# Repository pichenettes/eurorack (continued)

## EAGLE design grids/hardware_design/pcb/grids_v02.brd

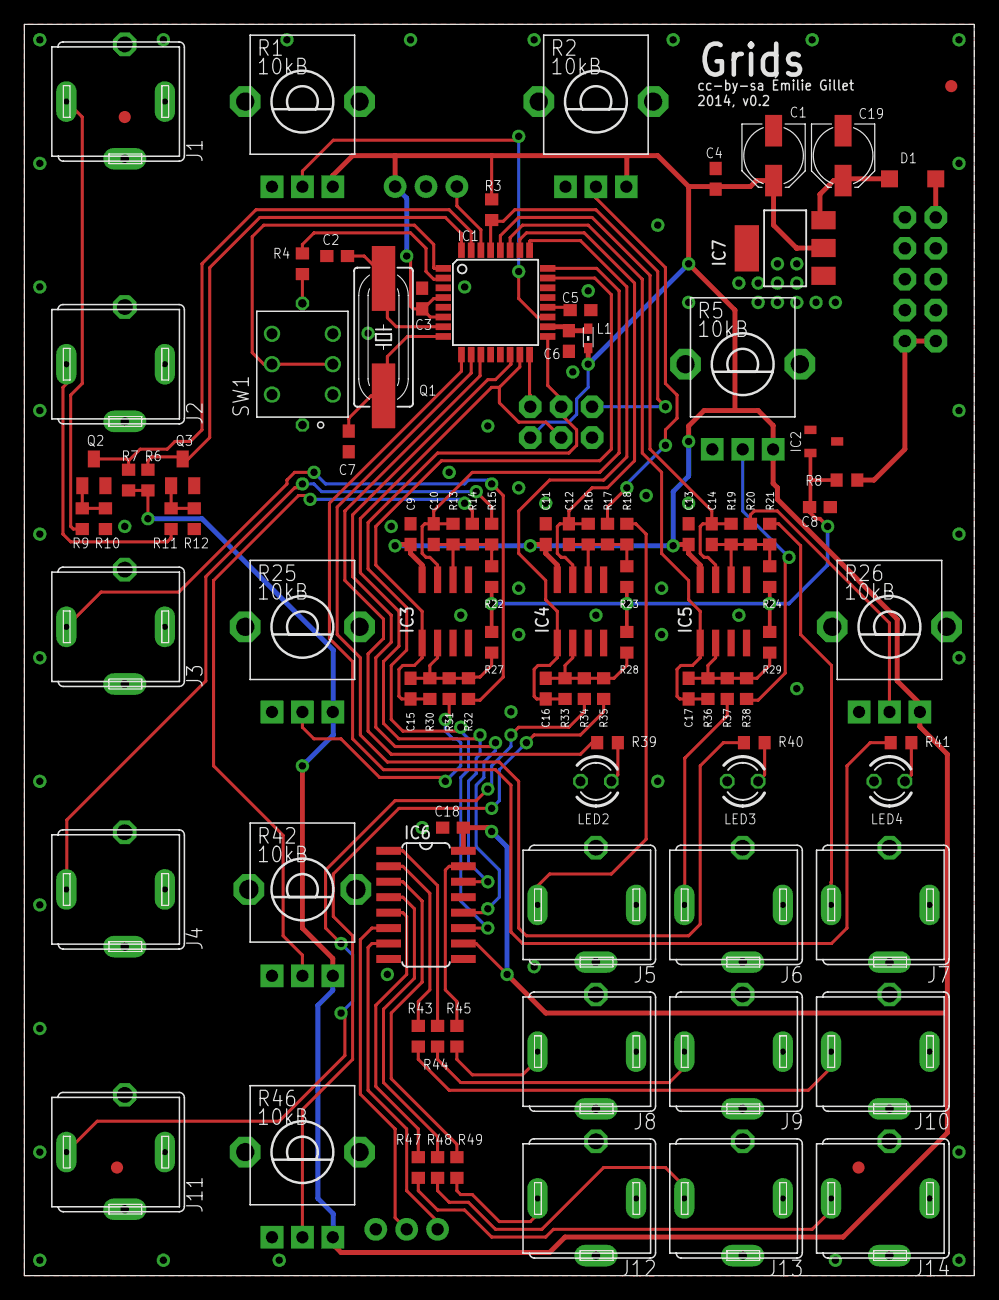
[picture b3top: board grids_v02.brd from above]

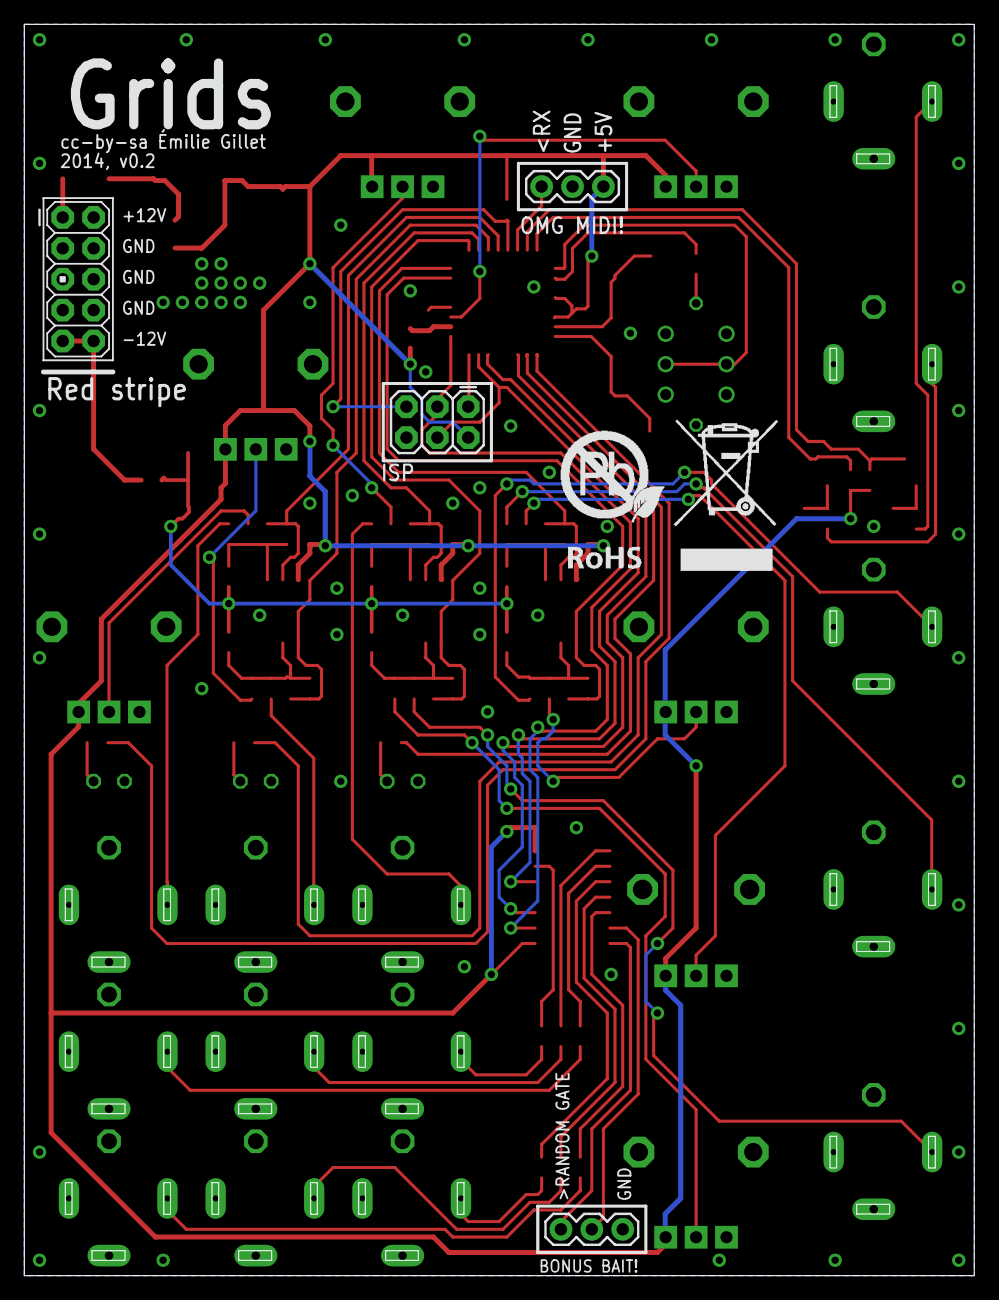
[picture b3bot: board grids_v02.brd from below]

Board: 2 copper layers, 78.1 x 102.9 mm, 108 parts (5 on the bottom side), 70 nets.

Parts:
C1, C19: 22u; PANASONIC_C
C2, C7: 18p; C0603
C3, C4, C5, C6, C9, C11, C13, C18: 100n; C0603
C8: 470n; C0603
C10, C12, C14, C15, C16, C17: 10n; C0603
D1: 1N5819HW; SOD123
F1, F2, F3, F4: FIDUCIAL1X2; FIDUCIAL-1X2
IC1: ATMEGA328P-AU; TQFP32-08
IC2: LM4040 5.0V; DBZ_R-PDSO-G3
IC3, IC4, IC5: MCP6002; SO08
IC6: 74HC595D; SO16
IC7: LM1117-5.0; SOT223
J1, J2, J3, J4, J5, J6, J7, J8, J9, J10, J11, J12, J13, J14: PJ301WQP; WQP_PJ_301BM
J15: 2X3
J16: M05X2PTH; AVR_ICSP
JP1, JP2: 1X03
L1: 0603
LED2, LED3, LED4: LED3MM
Q1: 20MHz; HC49UP
Q2, Q3: MMBT3904; SOT23-BEC
R1, R2, R5, R25, R26, R46: 10kB; ALPS_POT_VERTICAL_PS
R3, R6, R7, R8: 10k; R0603
R4, R39, R40, R41: 100; R0603
R9, R11, R13, R14, R15, R16, R17, R18, R19, R20, R21, R22, R23, R24, R27, R28, R29, R30, R31, R32, R33, R34, R35, R36, R37, R38: 100k; R0603
R10, R12: 1M; R0603
R42: 10kB; ALPS_POT_VERTICAL_PS4
R43, R44, R45, R47, R48, R49: 1.0k; R0603
SW1: LP4OA1PBCT
U$1: EURORACK_TEMPLATE
U$2: ROHS_BIG

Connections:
+5V: C1.+, C3.1, C4.1, C9.1, C11.1, C13.1, C18.1, IC1.4, IC1.6, IC3.8, IC4.8, IC5.8, IC6.10, IC6.16, IC7.2, J15.2, JP2.3, L1.1, R1.P$1, R2.P$1, R3.2, R5.P$1, R6.2, R7.2, R25.P$1, R26.P$1, R42.P$1, R46.P$1
AREF: C5.1, IC1.20
CH1_CV: C12.2, IC1.26, IC4.7, R16.2
CH2_CV: C17.2, IC1.27, IC5.1, R36.2
CH3_CV: C14.2, IC1.28, IC5.7, R19.2
CLOCK_OUT: IC6.6, JP1.2
GATE1_IN: J1.TIP, R9.2
GATE1_LED: R4.2, SW1.L1
GATE2_IN: J2.TIP, R11.2
GATE2_LED: LED4.A, R41.2
GATE3_LED: LED3.A, R40.2
GATE4_LED: LED2.A, R39.2
GND: C1.-, C2.1, C3.2, C4.2, C5.2, C6.2, C7.1, C8.2, C9.2, C11.2, C13.2, C18.2, C19.-, IC1.3, IC1.5, IC1.21, IC2.1, IC3.3, IC3.4, IC3.5, IC4.3, IC4.4, IC4.5, IC5.3, IC5.4, IC5.5, IC6.8, IC6.13, IC7.1, J1.GND, J1.GND2, J2.GND, J2.GND2, J3.GND, J3.GND2, J4.GND, J4.GND2, J5.GND, J5.GND2, J6.GND, J6.GND2, J7.GND, J7.GND2, J8.GND, J8.GND2, J9.GND, J9.GND2, J10.GND, J10.GND2, J11.GND, J11.GND2, J12.GND, J12.GND2, J13.GND, J13.GND2, J14.GND, J14.GND2, J15.6, J16.3, J16.4, J16.5, J16.6, J16.7, J16.8, JP1.1, JP2.2, LED2.K, LED3.K, LED4.K, Q2.E, Q3.E, R1.P$3, R2.P$3, R5.P$3, R10.1, R12.1, R25.P$3, R26.P$3, R42.P$3, R46.P$3, SW1.L2, SW1.P3, SW1.P6
IN_CLOCK: IC1.31, Q2.C, R7.1
IN_MIDI: IC1.30, JP2.1
IN_RESET: IC1.32, Q3.C, R6.1
LED_CH1: IC1.11, R39.1
LED_CH2: IC1.10, R40.1
LED_CH3: IC1.9, R41.1
LED_CLOCK: IC1.2, R4.1
MISO: IC1.16, J15.1
MOSI: IC1.15, IC6.14, J15.4
unnamed: Q2.B, R9.1, R10.2
unnamed: Q3.B, R11.1, R12.2
unnamed: D1.A, J16.1
unnamed: J14.TIP, R47.2
unnamed: J13.TIP, R48.2
unnamed: J12.TIP, R49.2
unnamed: R25.P$2, R31.1
unnamed: J3.TIP, R32.1
unnamed: C10.1, IC3.6, R13.1, R14.2, R15.2, R22.2
unnamed: R14.1, R42.P$2
unnamed: J4.TIP, R15.1
unnamed: C16.1, IC4.2, R28.2, R33.1, R34.2, R35.2
unnamed: R35.1, R46.P$2
unnamed: J11.TIP, R34.1
unnamed: C12.1, IC4.6, R16.1, R17.2, R18.2, R23.2
unnamed: R2.P$2, R17.1
unnamed: J5.TIP, R18.1
unnamed: C17.1, IC5.2, R29.2, R36.1, R37.2, R38.2
unnamed: R5.P$2, R38.1
unnamed: J6.TIP, R37.1
unnamed: C14.1, IC5.6, R19.1, R20.2, R21.2, R24.2
unnamed: R20.1, R26.P$2
unnamed: J7.TIP, R21.1
unnamed: IC6.15, R45.1
unnamed: IC6.1, R44.1
unnamed: C15.1, IC3.2, R27.2, R30.1, R31.2, R32.2
unnamed: IC6.2, R43.1
unnamed: IC6.3, R49.1
unnamed: IC6.4, R48.1
unnamed: IC6.5, R47.1
unnamed: J8.TIP, R45.2
unnamed: J9.TIP, R44.2
unnamed: J10.TIP, R43.2
unnamed: C6.1, IC1.18, L1.2
unnamed: C7.2, IC1.8, Q1.1
unnamed: C2.2, IC1.7, Q1.2
RANDOM_GATE: IC6.7, JP1.3
REF_-5: C8.1, IC2.2, R8.2, R22.1, R23.1, R24.1, R27.1, R28.1, R29.1
RESET: IC1.29, J15.5, R3.1
RND_CV: C16.2, IC1.25, IC4.1, R33.2
SCK: IC1.17, IC6.11, J15.3
SS: IC1.14, IC6.12
SW_RESET: IC1.1, SW1.P2, SW1.P5
TEMPO: IC1.19, R1.P$2
VCC: C19.+, D1.C, IC7.3
VEE: J16.9, J16.10, R8.1
X_CV: C15.2, IC1.23, IC3.1, R30.2
Y_CV: C10.2, IC1.24, IC3.7, R13.2

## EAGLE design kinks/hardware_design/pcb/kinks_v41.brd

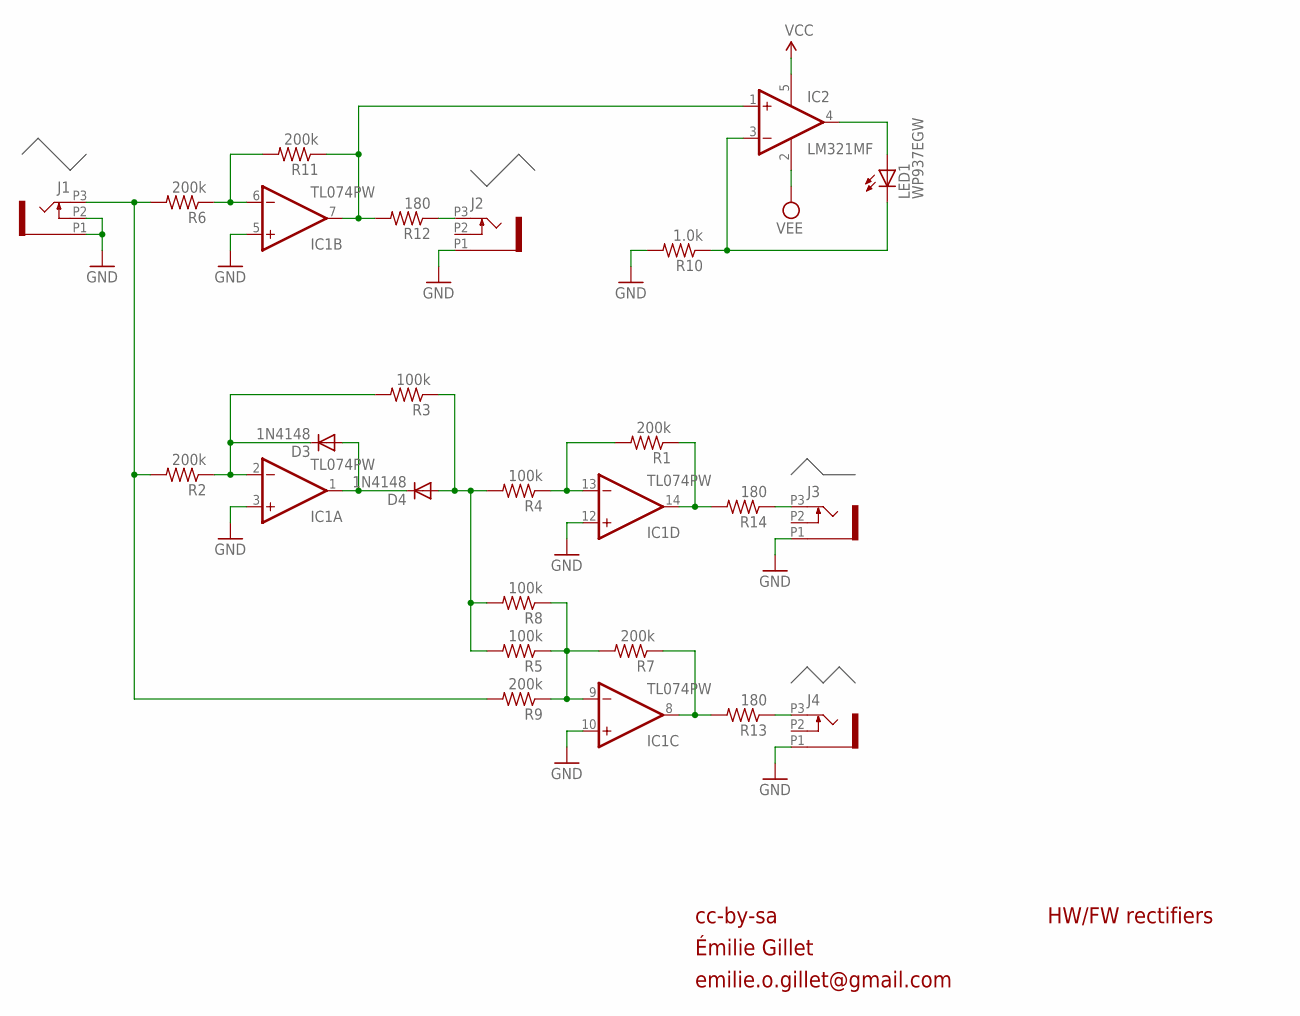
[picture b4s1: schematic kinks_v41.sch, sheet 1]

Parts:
D3, D4: 1N4148; SOD523
IC1: TL074PW; TSSOP14
IC2: LM321MF; SOT23-5
J1, J2, J3, J4: PJ301_THONKICONN6; WQP_PJ_301M6
LED1: WP937EGW; LED3MM
R1, R2, R6, R7, R9, R11: 200k; R0402
R3, R4, R5, R8: 100k; R0402
R10: 1.0k; R0402
R12, R13, R14: 180; R0402

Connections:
GND: IC1.3 (+IN), IC1.5 (+IN), IC1.10 (+IN), IC1.12 (+IN), J1.P1 (1), J1.P2 (2), J2.P1 (1), J3.P1 (1), J4.P1 (1), R10.2; also elsewhere on the board
unnamed: IC2.3 (-IN), LED1.K (C), R10.1
unnamed: IC2.4 (OUT), LED1.A
unnamed: IC1.6 (-IN), R6.1, R11.2
unnamed: IC1.7 (OUT), IC2.1 (+IN), R11.1, R12.2
unnamed: J2.P3 (3), R12.1
unnamed: D3.C, IC1.2 (-IN), R2.1, R3.2
unnamed: D3.A, D4.C, IC1.1 (OUT)
unnamed: IC1.14 (OUT), R1.1, R14.2
unnamed: IC1.13 (-IN), R1.2, R4.1
unnamed: J3.P3 (3), R14.1
unnamed: IC1.9 (-IN), R5.1, R7.2, R8.1, R9.1
unnamed: J4.P3 (3), R13.1
unnamed: IC1.8 (OUT), R7.1, R13.2
unnamed: J1.P3 (3), R2.2, R6.2, R9.2
unnamed: D4.A, R3.1, R4.2, R5.2, R8.2
VCC: IC2.5 (V+); also elsewhere on the board
VEE: IC2.2 (V-); also elsewhere on the board

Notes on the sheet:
cc-by-sa
HW/FW rectifiers
Émilie Gillet
emilie.o.gillet@gmail.com

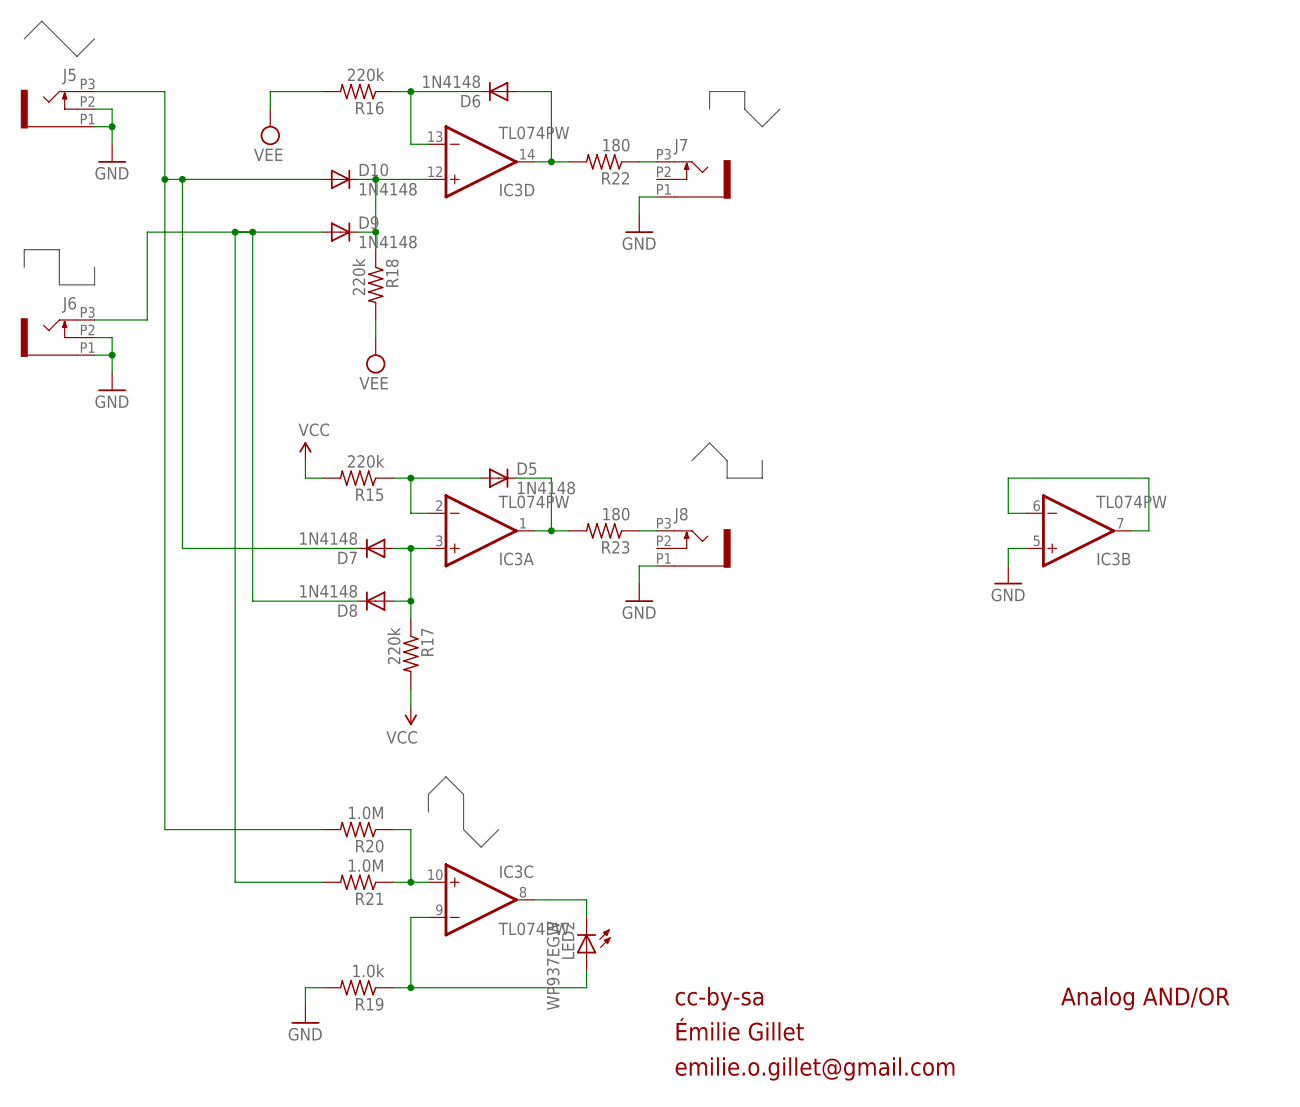
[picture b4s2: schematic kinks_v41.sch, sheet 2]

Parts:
D5, D6, D7, D8, D9, D10: 1N4148; SOD523
IC3: TL074PW; TSSOP14
J5, J6, J7, J8: PJ301_THONKICONN6; WQP_PJ_301M6
LED2: WP937EGW; LED3MM
R15, R16, R17, R18: 220k; R0402
R19: 1.0k; R0402
R20, R21: 1.0M; R0402
R22, R23: 180; R0402

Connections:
A: D7.C, D10.A, J5.P3 (3), R20.2
B: D8.C, D9.A, J6.P3 (3), R21.2
GND: IC3.5 (+IN), J5.P1 (1), J5.P2 (2), J6.P1 (1), J6.P2 (2), J7.P1 (1), J8.P1 (1), R19.2; also elsewhere on the board
unnamed: D9.C, D10.C, IC3.12 (+IN), R18.1
unnamed: D6.A, IC3.14 (OUT), R22.2
unnamed: D6.C, IC3.13 (-IN), R16.1
unnamed: D7.A, D8.A, IC3.3 (+IN), R17.1
unnamed: IC3.6 (-IN), IC3.7 (OUT)
unnamed: D5.C, IC3.1 (OUT), R23.2
unnamed: IC3.8 (OUT), LED2.K (C)
unnamed: D5.A, IC3.2 (-IN), R15.1
unnamed: J8.P3 (3), R23.1
unnamed: IC3.10 (+IN), R20.1, R21.1
unnamed: IC3.9 (-IN), LED2.A, R19.1
unnamed: J7.P3 (3), R22.1
VCC: R15.2, R17.2; also elsewhere on the board
VEE: R16.2, R18.2; also elsewhere on the board

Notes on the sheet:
cc-by-sa
Analog AND/OR
Émilie Gillet
emilie.o.gillet@gmail.com

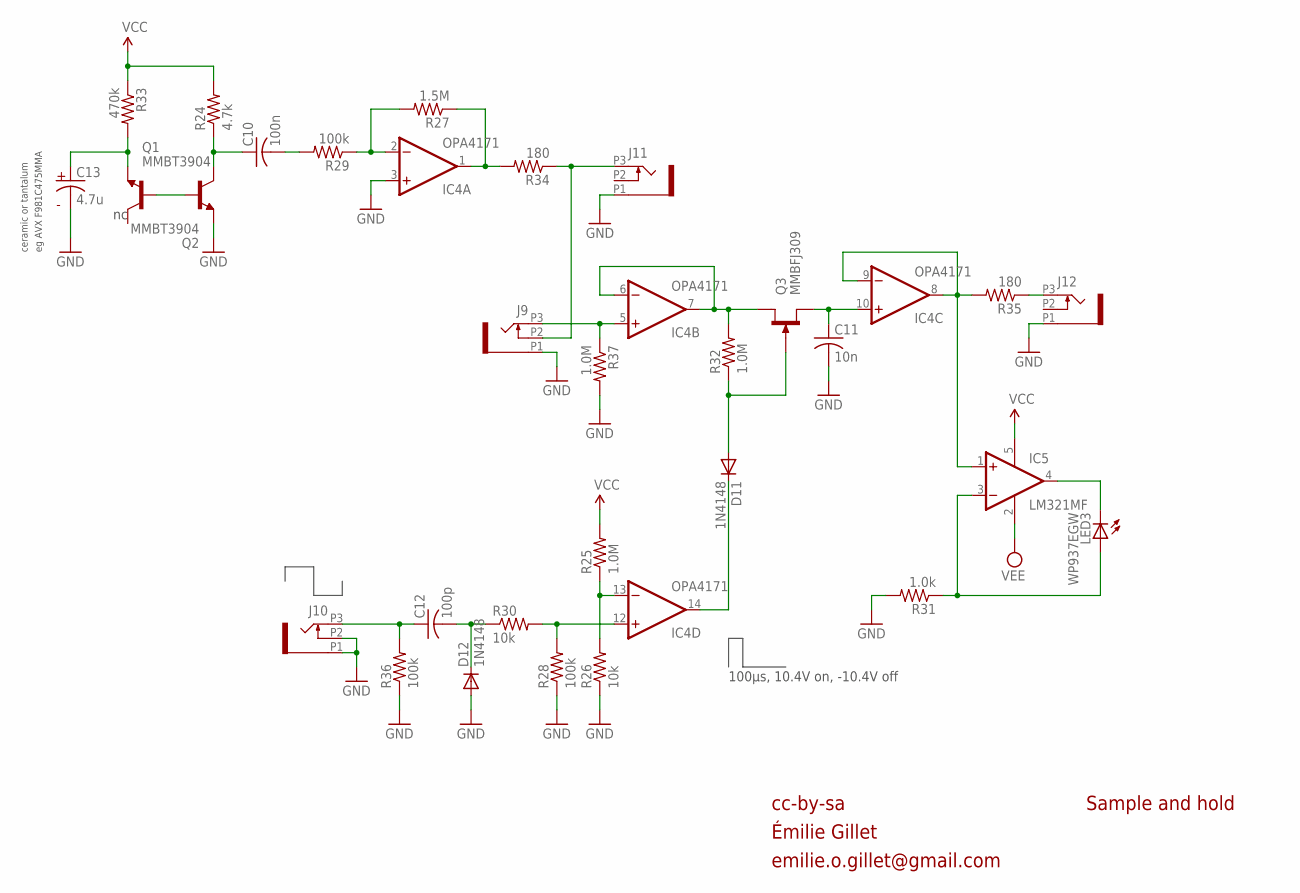
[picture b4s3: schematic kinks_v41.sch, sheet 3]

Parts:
C10: 100n; C0402
C11: 10n; C0603
C12: 100p; C0402
C13: 4.7u; C0603
D11, D12: 1N4148; SOD523
IC4: OPA4171; TSSOP14
IC5: LM321MF; SOT23-5
J9, J10, J11, J12: PJ301_THONKICONN6; WQP_PJ_301M6
LED3: WP937EGW; LED3MM
Q1, Q2: MMBT3904; SOT23-BEC
Q3: MMBFJ309; SOT23
R24: 4.7k; R0402
R25, R32, R37: 1.0M; R0402
R26, R30: 10k; R0402
R27: 1.5M; R0402
R28, R29, R36: 100k; R0402
R31: 1.0k; R0402
R33: 470k; R0402
R34, R35: 180; R0402

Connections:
GND: C11.2, C13.2, D12.A, IC4.3 (+IN), J9.P1 (1), J10.P1 (1), J10.P2 (2), J11.P1 (1), J12.P1 (1), Q1.E, R26.1, R28.1, R31.2, R36.1, R37.2; also elsewhere on the board
unnamed: IC4.8 (OUT), IC4.9 (-IN), IC5.1 (+IN), R35.2
unnamed: Q1.B, Q2.B
unnamed: C13.1, Q2.E, R33.2
unnamed: C10.2, R29.2
unnamed: IC4.2 (-IN), R27.2, R29.1
unnamed: IC5.3 (-IN), LED3.A, R31.1
unnamed: IC5.4 (OUT), LED3.K (C)
unnamed: C10.1, Q1.C, R24.1
unnamed: IC4.1 (OUT), R27.1, R34.2
unnamed: J9.P2 (2), J11.P3 (3), R34.1
unnamed: IC4.5 (+IN), J9.P3 (3), R37.1
unnamed: IC4.6 (-IN), IC4.7 (OUT), Q3.1 (D), R32.2
unnamed: D11.A, Q3.3 (G), R32.1
unnamed: D11.C, IC4.14 (OUT)
unnamed: C11.1, IC4.10 (+IN), Q3.2 (S)
unnamed: IC4.12 (+IN), R28.2, R30.2
unnamed: J12.P3 (3), R35.1
unnamed: C12.1, J10.P3 (3), R36.2
unnamed: IC4.13 (-IN), R25.1, R26.2
unnamed: C12.2, D12.C, R30.1
VCC: IC5.5 (V+), R24.2, R25.2, R33.1; also elsewhere on the board
VEE: IC5.2 (V-); also elsewhere on the board

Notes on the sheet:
cc-by-sa
Sample and hold
100µs, 10.4V on, -10.4V off
eg AVX F981C475MMA
ceramic or tantalum
Émilie Gillet
emilie.o.gillet@gmail.com

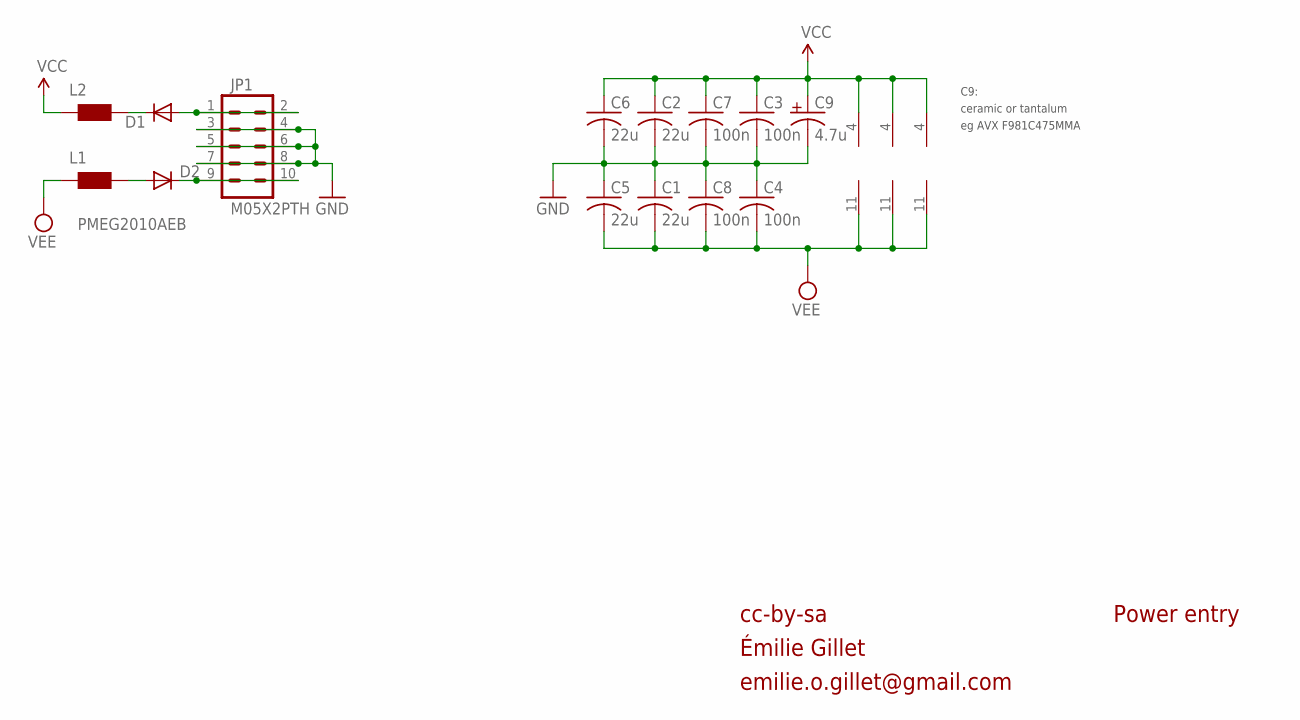
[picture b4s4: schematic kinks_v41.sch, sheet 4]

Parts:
C1, C2, C5, C6: 22u; C0805
C3, C4, C7, C8: 100n; C0402
C9: 4.7u; C0603
D1, D2: PMEG2010AEB; SOD523
IC1, IC3: TL074PW; TSSOP14
IC4: OPA4171; TSSOP14
JP1: M05X2PTH; AVR_ICSP
L1, L2: WE-CBF_0603; 0603

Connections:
GND: C1.1, C2.2, C3.2, C4.1, C5.1, C6.2, C7.2, C8.1, C9.2, JP1.3, JP1.4, JP1.5, JP1.6, JP1.7, JP1.8; also elsewhere on the board
unnamed: D1.A, JP1.1, JP1.2
unnamed: D2.C, JP1.9, JP1.10
unnamed: D1.C, L2.2
unnamed: D2.A, L1.2
VCC: C2.1, C3.1, C6.1, C7.1, C9.1, IC1.4 (V+), IC3.4 (V+), IC4.4 (V+), L2.1; also elsewhere on the board
VEE: C1.2, C4.2, C5.2, C8.2, IC1.11 (V-), IC3.11 (V-), IC4.11 (V-), L1.1; also elsewhere on the board

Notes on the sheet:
cc-by-sa
Power entry
eg AVX F981C475MMA
ceramic or tantalum
C9:
Émilie Gillet
emilie.o.gillet@gmail.com

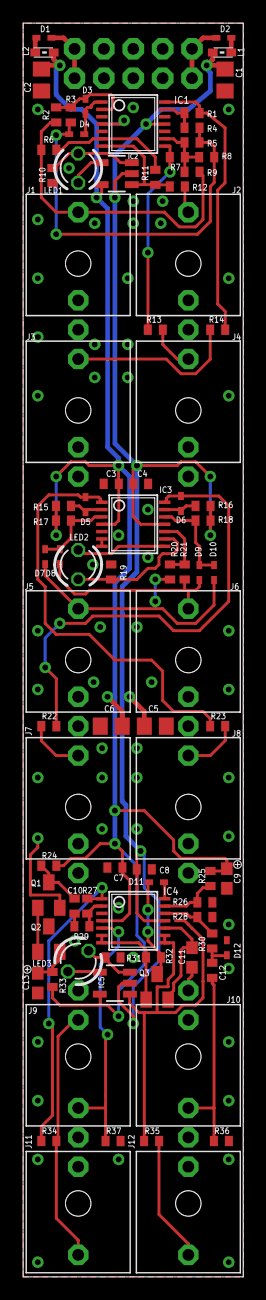
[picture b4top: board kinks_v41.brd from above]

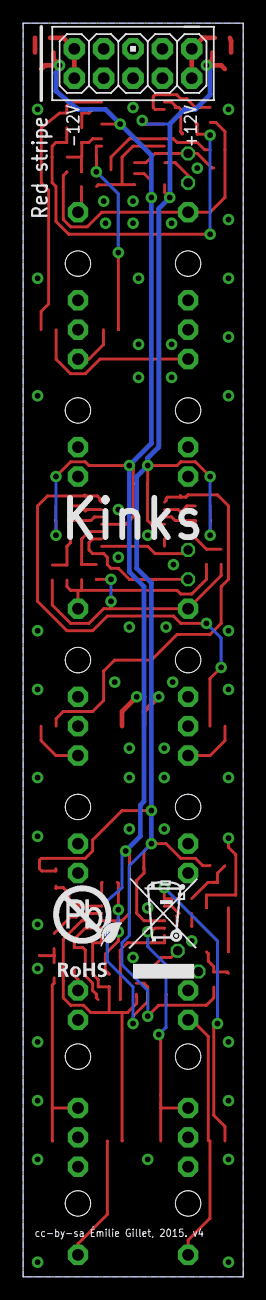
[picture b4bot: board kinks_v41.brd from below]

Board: 2 copper layers, 19.0 x 108.4 mm, 89 parts (2 on the bottom side), 56 nets.

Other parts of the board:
U$2: ROHS

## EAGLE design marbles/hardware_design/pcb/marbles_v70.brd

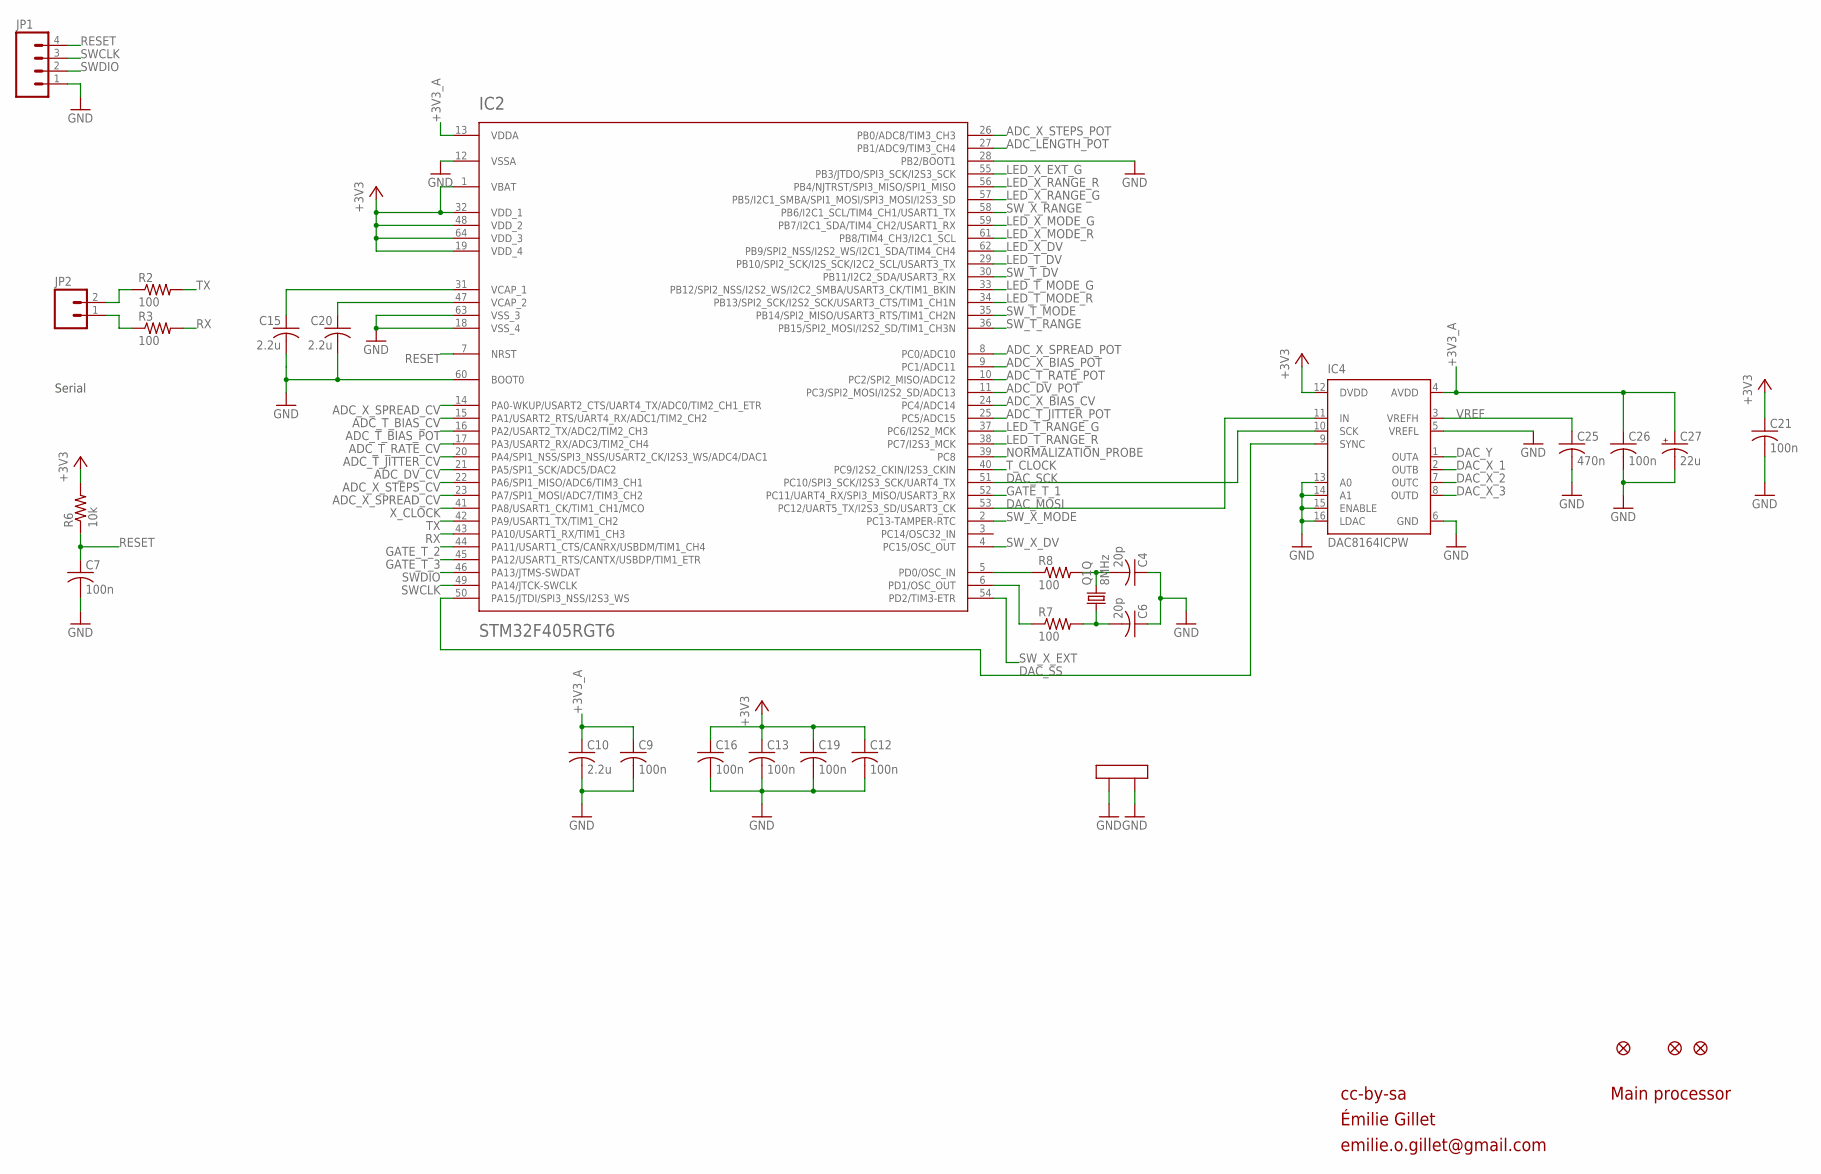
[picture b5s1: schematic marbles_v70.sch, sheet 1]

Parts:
C4, C6: 20p; C0402
C7, C9, C12, C13, C16, C19, C21, C26: 100n; C0402
C10, C15, C20: 2.2u; C0805
C25: 470n; C0402
C27: 22u; PANASONIC_C
F1, F2, F3: FIDUCIAL1X2; FIDUCIAL-1X2
IC2: STM32F405RGT6; TQFP-10X10-64
IC4: DAC8164ICPW; SOP65P640X110-16N
JP1: M04PTH; 1X04
JP2: M02PTH; 1X02
Q1: 8MHz; CTS406
R2, R3, R7, R8: 100; R0402
R6: 10k; R0402

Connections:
+3V3: C12.1, C13.1, C16.1, C19.1, C21.1, IC2.1 (VBAT), IC2.19 (VDD_4), IC2.32 (VDD_1), IC2.48 (VDD_2), IC2.64 (VDD_3), IC4.12 (DVDD), R6.2; also elsewhere on the board
+3V3_A: C9.1, C10.1, C26.1, C27.+, IC2.13 (VDDA), IC4.4 (AVDD); also elsewhere on the board
ADC_DV_CV: IC2.21 (PA5/SPI1_SCK/ADC5/DAC2); also elsewhere on the board
ADC_DV_POT: IC2.11 (PC3/SPI2_MOSI/I2S2_SD/ADC13); also elsewhere on the board
ADC_LENGTH_POT: IC2.27 (PB1/ADC9/TIM3_CH4); also elsewhere on the board
ADC_T_BIAS_CV: IC2.15 (PA1/USART2_RTS/UART4_RX/ADC1/TIM2_CH2); also elsewhere on the board
ADC_T_BIAS_POT: IC2.16 (PA2/USART2_TX/ADC2/TIM2_CH3); also elsewhere on the board
ADC_T_JITTER_CV: IC2.20 (PA4/SPI1_NSS/SPI3_NSS/USART2_CK/I2S3_WS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); also elsewhere on the board
ADC_T_JITTER_POT: IC2.25 (PC5/ADC15); also elsewhere on the board
ADC_T_RATE_CV: IC2.17 (PA3/USART2_RX/ADC3/TIM2_CH4); also elsewhere on the board
ADC_T_RATE_POT: IC2.10 (PC2/SPI2_MISO/ADC12); also elsewhere on the board
ADC_X_BIAS_CV: IC2.24 (PC4/ADC14); also elsewhere on the board
ADC_X_BIAS_POT: IC2.9 (PC1/ADC11); also elsewhere on the board
ADC_X_SPREAD_CV: IC2.14 (PA0-WKUP/USART2_CTS/UART4_TX/ADC0/TIM2_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), IC2.23 (PA7/SPI1_MOSI/ADC7/TIM3_CH2); also elsewhere on the board
ADC_X_SPREAD_POT: IC2.8 (PC0/ADC10); also elsewhere on the board
ADC_X_STEPS_CV: IC2.22 (PA6/SPI1_MISO/ADC6/TIM3_CH1); also elsewhere on the board
ADC_X_STEPS_POT: IC2.26 (PB0/ADC8/TIM3_CH3); also elsewhere on the board
DAC_MOSI: IC2.53 (PC12/UART5_TX/I2S3_SD/USART3_CK), IC4.11 (IN)
DAC_SCK: IC2.51 (PC10/SPI3_SCK/I2S3_SCK/UART4_TX), IC4.10 (SCK)
DAC_SS: IC2.50 (PA15/JTDI/SPI3_NSS/I2S3_WS), IC4.9 (SYNC)
DAC_X_1: IC4.2 (OUTB); also elsewhere on the board
DAC_X_2: IC4.7 (OUTC); also elsewhere on the board
DAC_X_3: IC4.8 (OUTD); also elsewhere on the board
DAC_Y: IC4.1 (OUTA); also elsewhere on the board
GATE_T_1: IC2.52 (PC11/UART4_RX/SPI3_MISO/USART3_RX); also elsewhere on the board
GATE_T_2: IC2.44 (PA11/USART1_CTS/CANRX/USBDM/TIM1_CH4); also elsewhere on the board
GATE_T_3: IC2.45 (PA12/USART1_RTS/CANTX/USBDP/TIM1_ETR); also elsewhere on the board
GND: C4.1, C6.1, C7.2, C9.2, C10.2, C12.2, C13.2, C15.2, C16.2, C19.2, C20.2, C21.2, C25.2, C26.2, C27.-, IC2.12 (VSSA), IC2.18 (VSS_4), IC2.28 (PB2/BOOT1), IC2.60 (BOOT0), IC2.63 (VSS_3), IC4.5 (VREFL), IC4.6 (GND), IC4.13 (A0), IC4.14 (A1), IC4.15 (ENABLE), IC4.16 (LDAC), JP1.1, Q1.2 (LID1), Q1.4 (LID2); also elsewhere on the board
LED_T_DV: IC2.29 (PB10/SPI2_SCK/I2S_SCK/I2C2_SCL/USART3_TX); also elsewhere on the board
LED_T_MODE_G: IC2.33 (PB12/SPI2_NSS/I2S2_WS/I2C2_SMBA/USART3_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); also elsewhere on the board
LED_T_MODE_R: IC2.34 (PB13/SPI2_SCK/I2S2_SCK/USART3_CTS/TIM1_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); also elsewhere on the board
LED_T_RANGE_G: IC2.37 (PC6/I2S2_MCK); also elsewhere on the board
LED_T_RANGE_R: IC2.38 (PC7/I2S3_MCK); also elsewhere on the board
LED_X_DV: IC2.62 (PB9/SPI2_NSS/I2S2_WS/I2C1_SDA/TIM4_CH4); also elsewhere on the board
LED_X_EXT_G: IC2.55 (PB3/JTDO/SPI3_SCK/I2S3_SCK); also elsewhere on the board
LED_X_MODE_G: IC2.59 (PB7/I2C1_SDA/TIM4_CH2/USART1_RX); also elsewhere on the board
LED_X_MODE_R: IC2.61 (PB8/TIM4_CH3/I2C1_SCL); also elsewhere on the board
LED_X_RANGE_G: IC2.57 (PB5/I2C1_SMBA/SPI1_MOSI/SPI3_MOSI/I2S3_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); also elsewhere on the board
LED_X_RANGE_R: IC2.56 (PB4/NJTRST/SPI3_MISO/SPI1_MISO); also elsewhere on the board
unnamed: IC2.6 (PD1/OSC_OUT), R7.1
unnamed: IC2.5 (PD0/OSC_IN), R8.1
unnamed: C20.1, IC2.47 (VCAP_2)
unnamed: C15.1, IC2.31 (VCAP_1)
unnamed: JP2.2, R2.1
unnamed: JP2.1, R3.1
unnamed: C4.2, Q1.3 (2), R8.2
unnamed: C6.2, Q1.1, R7.2
NORMALIZATION_PROBE: IC2.39 (PC8); also elsewhere on the board
RESET: C7.1, IC2.7 (NRST), JP1.4, R6.1
RX: IC2.43 (PA10/USART1_RX/TIM1_CH3), R3.2
SWCLK: IC2.49 (PA14/JTCK-SWCLK), JP1.3
SWDIO: IC2.46 (PA13/JTMS-SWDAT), JP1.2
SW_T_DV: IC2.30 (PB11/I2C2_SDA/USART3_RX); also elsewhere on the board
SW_T_MODE: IC2.35 (PB14/SPI2_MISO/USART3_RTS/TIM1_CH2N); also elsewhere on the board
SW_T_RANGE: IC2.36 (PB15/SPI2_MOSI/I2S2_SD/TIM1_CH3N); also elsewhere on the board
SW_X_DV: IC2.4 (PC15/OSC_OUT); also elsewhere on the board
SW_X_EXT: IC2.54 (PD2/TIM3-ETR); also elsewhere on the board
SW_X_MODE: IC2.2 (PC13-TAMPER-RTC); also elsewhere on the board
SW_X_RANGE: IC2.58 (PB6/I2C1_SCL/TIM4_CH1/USART1_TX); also elsewhere on the board
TX: IC2.42 (PA9/USART1_TX/TIM1_CH2), R2.2
T_CLOCK: IC2.40 (PC9/I2S2_CKIN/I2S3_CKIN); also elsewhere on the board
VREF: C25.1, IC4.3 (VREFH); also elsewhere on the board
X_CLOCK: IC2.41 (PA8/USART1_CK/TIM1_CH1/MCO); also elsewhere on the board

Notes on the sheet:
cc-by-sa
Main processor
Serial
Émilie Gillet
emilie.o.gillet@gmail.com

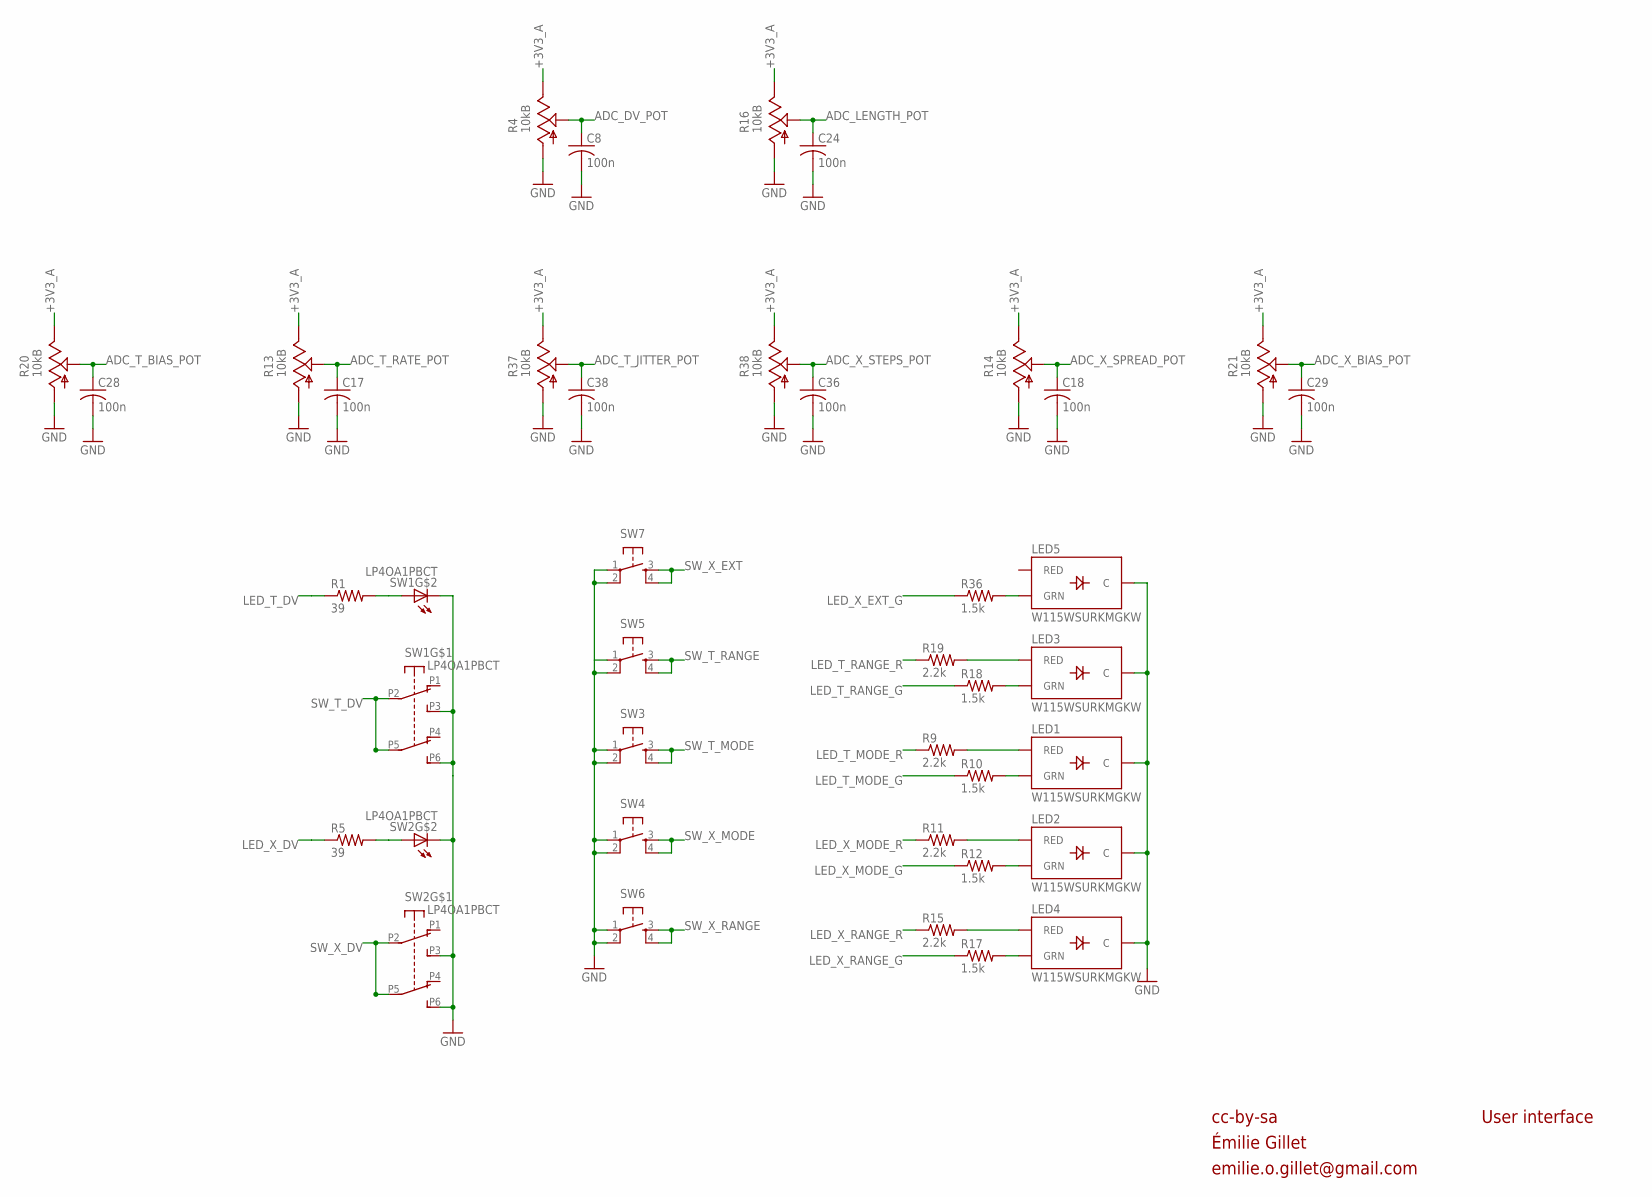
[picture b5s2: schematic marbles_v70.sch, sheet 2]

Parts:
C8, C17, C18, C24, C28, C29, C36, C38: 100n; C0402
LED1, LED2, LED3, LED4, LED5: W115WSURKMGKW; LED-BICOLOR-THROUGHHOLE-2.54
R1, R5: 39; R0402
R4, R13, R14, R16, R20, R21, R37, R38: 10kB; ALPS_POT_VERTICAL_PS
R9, R11, R15, R19: 2.2k; R0402
R10, R12, R17, R18, R36: 1.5k; R0402
SW1, SW2: LP4OA1PBCT
SW3, SW4, SW5, SW6, SW7: TAC_SWITCHPTH; TACTILE-PTH

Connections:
+3V3_A: R4.P$1 (E), R13.P$1 (E), R14.P$1 (E), R16.P$1 (E), R20.P$1 (E), R21.P$1 (E), R37.P$1 (E), R38.P$1 (E); also elsewhere on the board
ADC_DV_POT: C8.1, R4.P$2 (S); also elsewhere on the board
ADC_LENGTH_POT: C24.1, R16.P$2 (S); also elsewhere on the board
ADC_T_BIAS_POT: C28.1, R20.P$2 (S); also elsewhere on the board
ADC_T_JITTER_POT: C38.1, R37.P$2 (S); also elsewhere on the board
ADC_T_RATE_POT: C17.1, R13.P$2 (S); also elsewhere on the board
ADC_X_BIAS_POT: C29.1, R21.P$2 (S); also elsewhere on the board
ADC_X_SPREAD_POT: C18.1, R14.P$2 (S); also elsewhere on the board
ADC_X_STEPS_POT: C36.1, R38.P$2 (S); also elsewhere on the board
GND: C8.2, C17.2, C18.2, C24.2, C28.2, C29.2, C36.2, C38.2, LED1.2 (C), LED2.2 (C), LED3.2 (C), LED4.2 (C), LED5.2 (C), R4.P$3 (A), R13.P$3 (A), R14.P$3 (A), R16.P$3 (A), R20.P$3 (A), R21.P$3 (A), R37.P$3 (A), R38.P$3 (A), SW1.L2, SW1.P3 (A3), SW1.P6 (B3), SW2.L2, SW2.P3 (A3), SW2.P6 (B3), SW3.1, SW3.2, SW4.1, SW4.2, SW5.1, SW5.2, SW6.1, SW6.2, SW7.1, SW7.2; also elsewhere on the board
LED_T_DV: R1.1; also elsewhere on the board
LED_T_MODE_G: R10.1; also elsewhere on the board
LED_T_MODE_R: R9.1; also elsewhere on the board
LED_T_RANGE_G: R18.1; also elsewhere on the board
LED_T_RANGE_R: R19.1; also elsewhere on the board
LED_X_DV: R5.1; also elsewhere on the board
LED_X_EXT_G: R36.1; also elsewhere on the board
LED_X_MODE_G: R12.1; also elsewhere on the board
LED_X_MODE_R: R11.1; also elsewhere on the board
LED_X_RANGE_G: R17.1; also elsewhere on the board
LED_X_RANGE_R: R15.1; also elsewhere on the board
unnamed: R1.2, SW1.L1
unnamed: R5.2, SW2.L1
unnamed: LED3.3 (RED), R19.2
unnamed: LED3.1 (GRN), R18.2
unnamed: LED1.3 (RED), R9.2
unnamed: LED2.3 (RED), R11.2
unnamed: LED2.1 (GRN), R12.2
unnamed: LED4.3 (RED), R15.2
unnamed: LED1.1 (GRN), R10.2
unnamed: LED4.1 (GRN), R17.2
unnamed: LED5.1 (GRN), R36.2
SW_T_DV: SW1.P2 (A2), SW1.P5 (B2); also elsewhere on the board
SW_T_MODE: SW3.3, SW3.4; also elsewhere on the board
SW_T_RANGE: SW5.3, SW5.4; also elsewhere on the board
SW_X_DV: SW2.P2 (A2), SW2.P5 (B2); also elsewhere on the board
SW_X_EXT: SW7.3, SW7.4; also elsewhere on the board
SW_X_MODE: SW4.3, SW4.4; also elsewhere on the board
SW_X_RANGE: SW6.3, SW6.4; also elsewhere on the board

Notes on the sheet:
cc-by-sa
User interface
Émilie Gillet
emilie.o.gillet@gmail.com
